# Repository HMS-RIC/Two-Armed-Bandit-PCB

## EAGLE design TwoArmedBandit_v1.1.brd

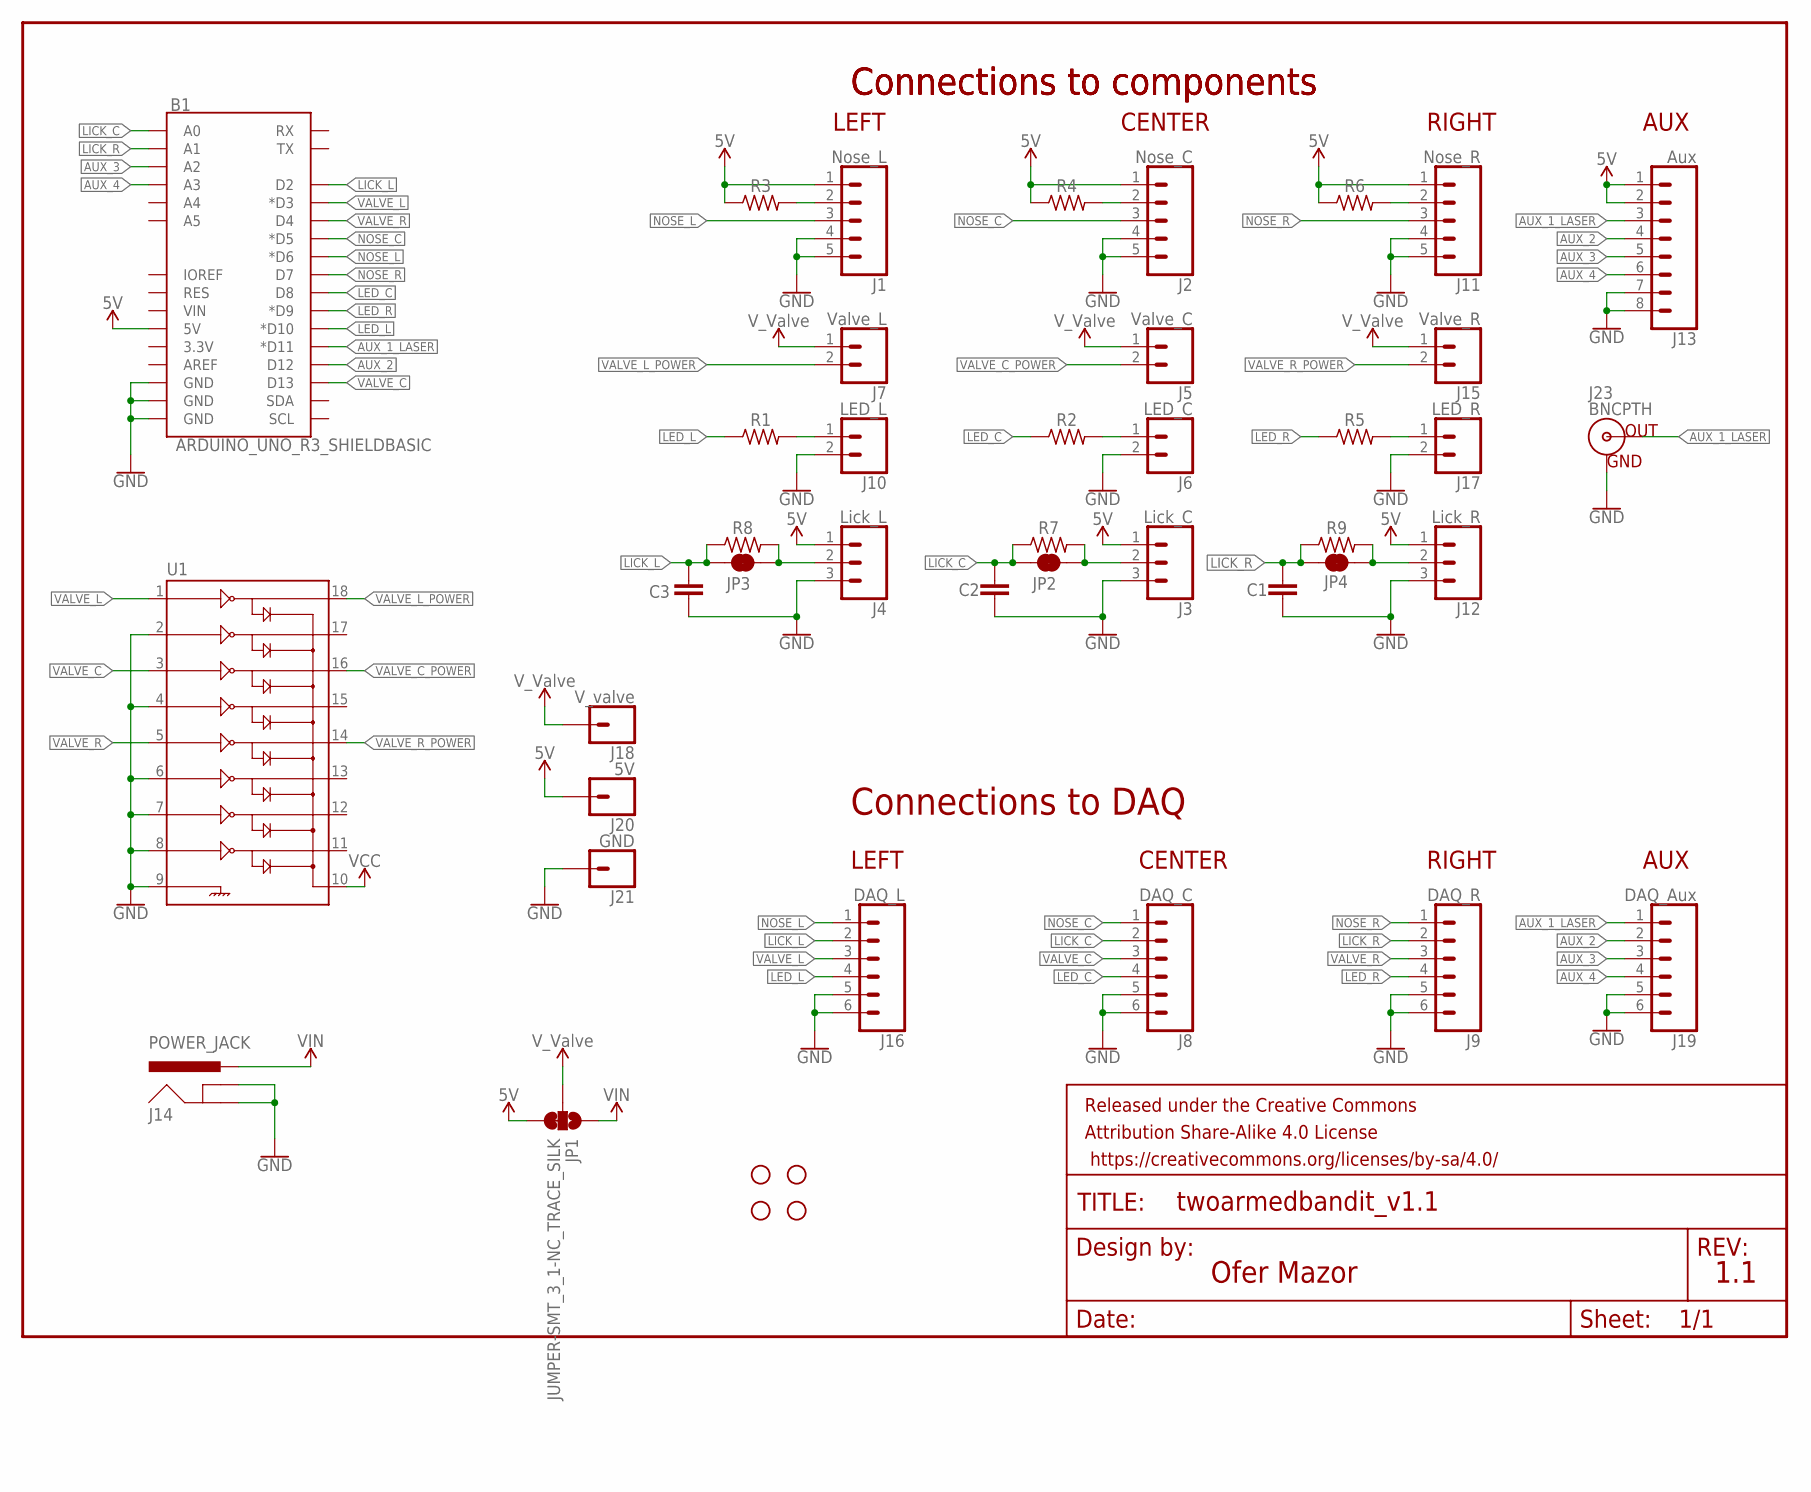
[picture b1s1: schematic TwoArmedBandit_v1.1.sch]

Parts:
B1: ARDUINO_UNO_R3_SHIELDBASIC; UNO_R3_SHIELD
C1, C2, C3: C5/2.5; C5B2.5
FRAME1: FRAME-LETTERNO_PACKAGE; DUMMY
H1, H2, H3, H4: STAND-OFF
J1: Nose_L; SCREWTERMINAL-3.5MM-5
J2: Nose_C; SCREWTERMINAL-3.5MM-5
J3: Lick_C; 1X03
J4: Lick_L; 1X03
J5: Valve_C; 1X02
J6: LED_C; 1X02
J7: Valve_L; 1X02
J8: DAQ_C; SCREWTERMINAL-3.5MM-6
J9: DAQ_R; SCREWTERMINAL-3.5MM-6
J10: LED_L; 1X02
J11: Nose_R; SCREWTERMINAL-3.5MM-5
J12: Lick_R; 1X03
J13: Aux; 1X08
J14: POWER_JACK; POWER_JACK_PTH
J15: Valve_R; 1X02
J16: DAQ_L; SCREWTERMINAL-3.5MM-6
J17: LED_R; 1X02
J18: V_valve; 1X01_2MM
J19: DAQ_Aux; SCREWTERMINAL-3.5MM-6
J20: 5V; 1X01_2MM
J21: GND; 1X01_2MM
J23: BNCPTH; BNC
JP1: JUMPER-SMT_3_1-NC_TRACE_SILK; SMT-JUMPER_3_1-NC_TRACE_SILK
JP2, JP3, JP4: JUMPER-SMT_2_NC_TRACE_NO-SILK; SMT-JUMPER_2_NC_TRACE_NO-SILK
R1, R2, R5: 330; 0309/12
R3, R4, R6, R7, R8, R9: 160; 0309/12
U1: ULN2803DIP; DIL18

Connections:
5V: B1.5V, J1.1, J2.1, J3.1, J4.1, J11.1, J12.1, J13.1, J13.2, J20.1, JP1.3, R3.1, R4.1, R6.1
AUX_1_LASER: B1.D11 (*D11), J13.3, J19.1, J23.S (OUT)
AUX_2: B1.D12, J13.4, J19.2
AUX_3: B1.A2, J13.5, J19.3
AUX_4: B1.A3, J13.6, J19.4
GND: B1.GND@0 (GND), B1.GND@1 (GND), B1.GND@2 (GND), C1.2, C2.2, C3.2, J1.4, J1.5, J2.4, J2.5, J3.3, J4.3, J6.2, J8.5, J8.6, J9.5, J9.6, J10.2, J11.4, J11.5, J12.3, J13.7, J13.8, J14.GND, J14.GNDBREAK, J16.5, J16.6, J17.2, J19.5, J19.6, J21.1, J23.GND, U1.2, U1.4, U1.6, U1.7, U1.8, U1.9
LED_C: B1.D8, J8.4, R2.1
LED_L: B1.D10 (*D10), J16.4, R1.1
LED_R: B1.D9 (*D9), J9.4, R5.1
LICK_C: B1.A0, C2.1, J8.2, JP2.1, R7.1
LICK_L: B1.D2, C3.1, J16.2, JP3.1, R8.1
LICK_R: B1.A1, C1.1, J9.2, JP4.1, R9.1
unnamed: J2.2, R4.2
unnamed: J1.2, R3.2
unnamed: J6.1, R2.2
unnamed: J11.2, R6.2
unnamed: J17.1, R5.2
unnamed: J12.2, JP4.2, R9.2
unnamed: J3.2, JP2.2, R7.2
unnamed: J4.2, JP3.2, R8.2
unnamed: J10.1, R1.2
NOSE_C: B1.D5 (*D5), J2.3, J8.1
NOSE_L: B1.D6 (*D6), J1.3, J16.1
NOSE_R: B1.D7, J9.1, J11.3
VALVE_C: B1.D13, J8.3, U1.3
VALVE_C_POWER: J5.2, U1.16
VALVE_L: B1.D3 (*D3), J16.3, U1.1
VALVE_L_POWER: J7.2, U1.18
VALVE_R: B1.D4, J9.3, U1.5
VALVE_R_POWER: J15.2, U1.14
VIN: J14.PWR, JP1.1
V_VALVE: J5.1, J7.1, J15.1, J18.1, JP1.2, U1.10

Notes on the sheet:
Connections to components
Connections to DAQ
LEFT
CENTER
RIGHT
AUX
Ofer Mazor
1.1

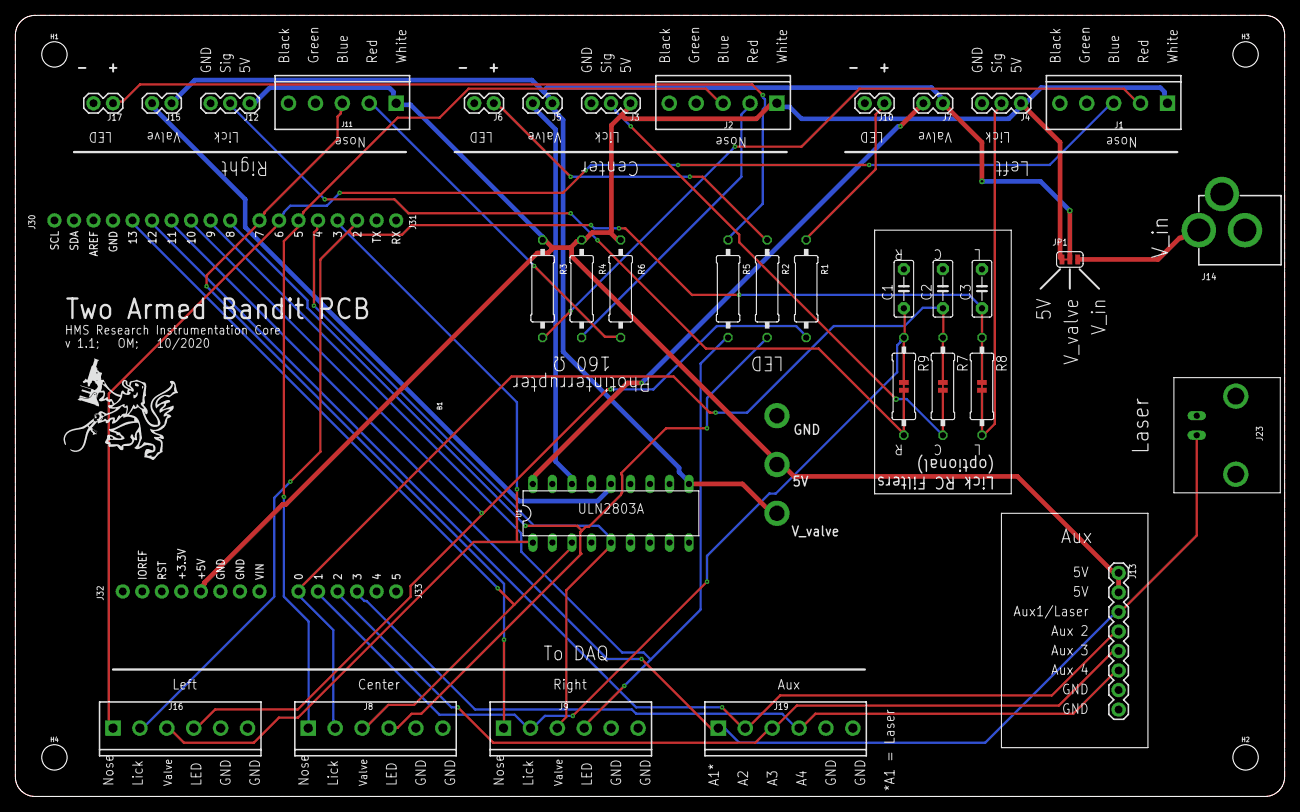
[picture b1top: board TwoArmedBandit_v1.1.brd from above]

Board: 2 copper layers, 165.1 x 101.6 mm, 46 parts (0 on the bottom side), 32 nets.

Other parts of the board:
U$1: RIC_LOGO_BIG

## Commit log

2020-07-29 Create LICENSE
2020-07-29 Remove old files
2020-07-29 Fix wiring of V_valve; Update version to v1.1
2020-07-29 Add standoffs to BOM
2020-07-29 Add PDF of schematic
2020-08-03 Added PinAssignments.txt
2020-10-22 Swap pins for Aux-1/Aux-2
    In order for Aux-1-Laser to have PWM, needed to change
    Aux-1 to D11 and Aux-2 to D12.
2020-10-22 Add optional RC filter to lick sensor output
2020-10-22 Minor board fixes
2020-10-27 Generate Gerbers and PDFs for v1.1
2020-12-07 Remove old file
2020-12-07 Update BOM for MTA-100 connectors
2023-10-31 Add outline file to Gerbers

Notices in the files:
parts and their libraries:
SparkFun-Boards: Licensing: Creative Commons ShareAlike 4.0 International - https://creativecommons.org/licenses/by-sa/4.0
SparkFun-Aesthetics: Released under the Creative Commons Attribution Share-Alike 4.0 License
SparkFun-Aesthetics: https://creativecommons.org/licenses/by-sa/4.0
